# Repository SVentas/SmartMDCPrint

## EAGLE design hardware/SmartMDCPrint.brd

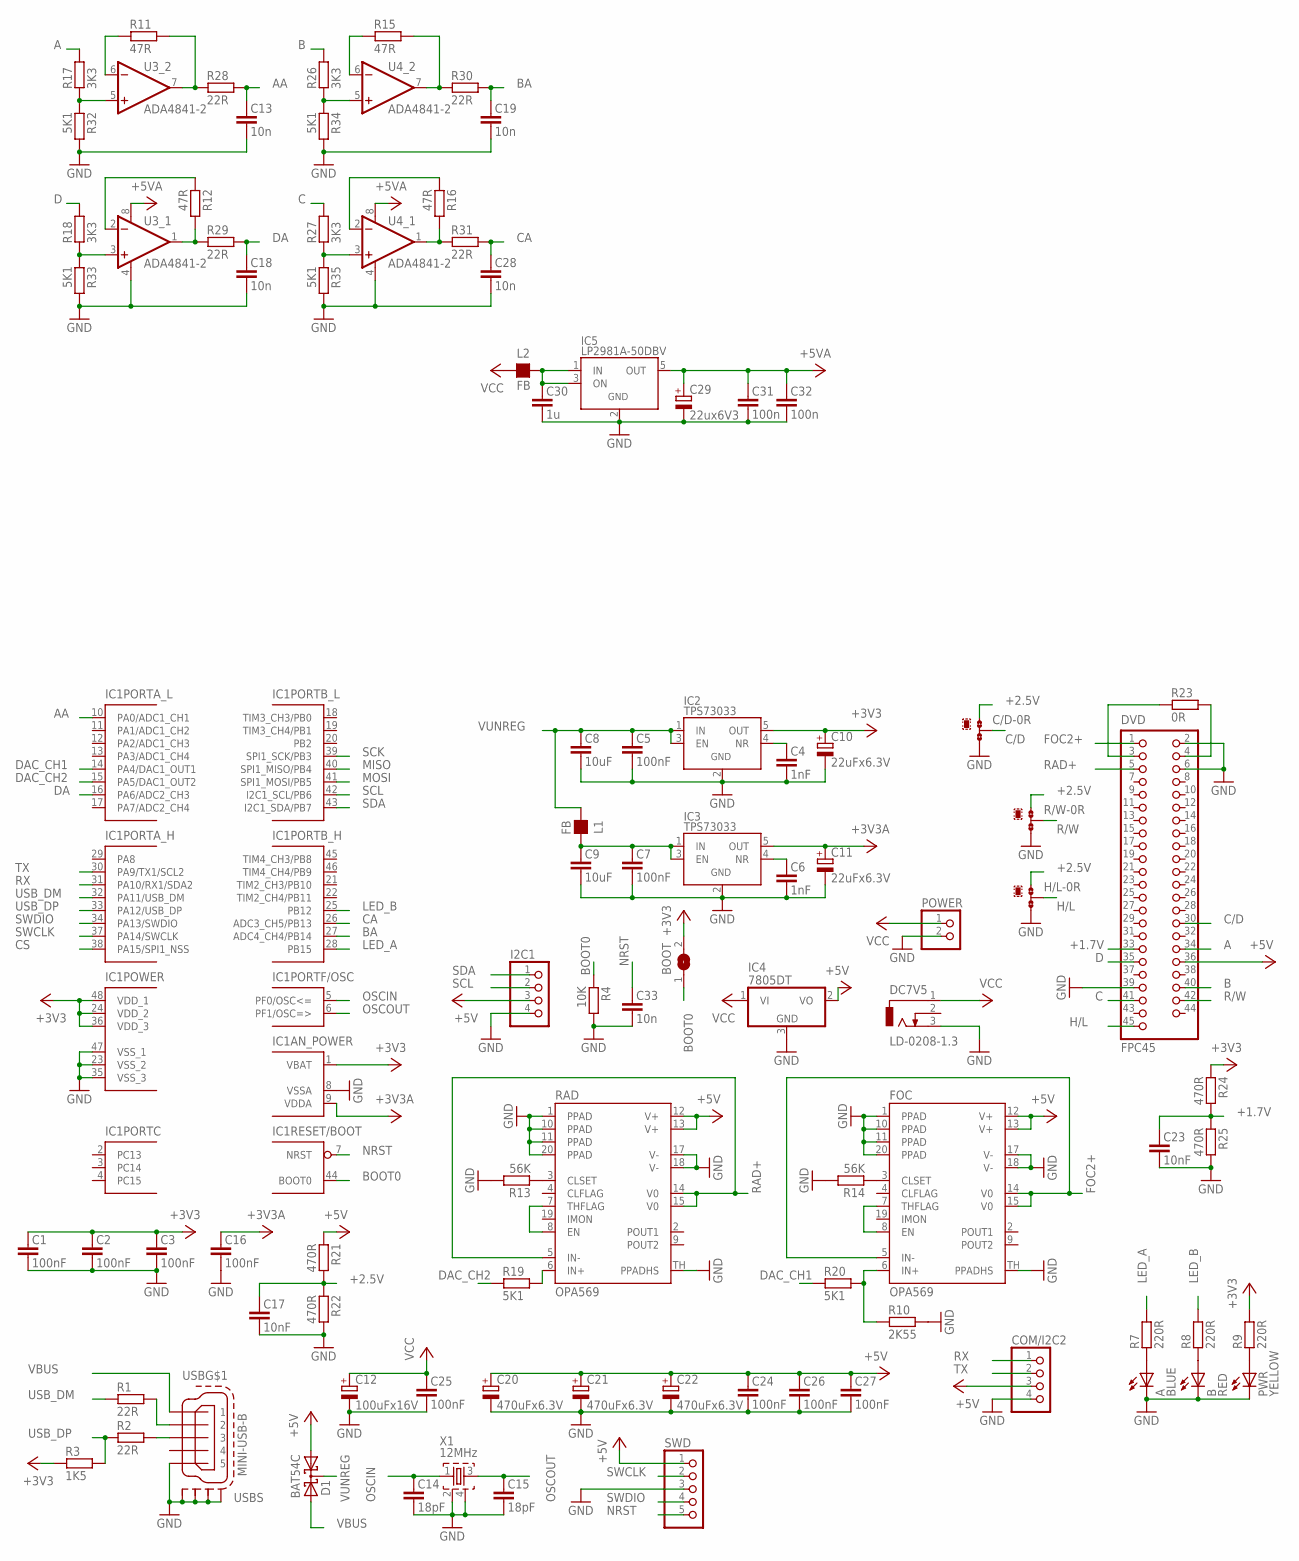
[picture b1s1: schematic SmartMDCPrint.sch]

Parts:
A: BLUE; CHIPLED_0805
B: RED; CHIPLED_0805
BOOT: SJ
C1, C2, C3, C5, C7, C16, C24, C25, C26, C27: 100nF; C0603G
C4, C6: 1nF; C0603G
C8, C9: 10uF; C0805
C10, C11: 22uFx6.3V; SMC_A
C12: 100uFx16V; E2,5-7
C13, C18, C19, C28, C33: 10n; C0603G
C14, C15: 18pF; C0603G
C17, C23: 10nF; C0603G
C20, C21, C22: 470uFx6.3V; SMC_D
C29: 22ux6V3; SMC_A
C30: 1u; C0603G
C31, C32: 100n; C0603G
C/D: 0R-JUMPA; A0R-JMP
COM/I2C2: PINHD-1X4; 1X04
D1: BAT54C; SOT23
DC7V5: LD-0208-1.3; LD-0208
DVD: FPC45
FOC: OPA569; SO-20
H/L: 0R-JUMPA; A0R-JMP
I2C1: PINHD-1X4; 1X04
IC1: STM32F303CCT6; LQFP48
IC2, IC3: TPS73033; SOT23-5
IC4: 7805DT; TO252
IC5: LP2981A-50DBV; SOT23-5
L1, L2: FB; L0603
POWER: PINHD-1X2; 1X02
PWR: YELLOW; CHIPLED_0805
R1, R2, R28, R29, R30, R31: 22R; R0603
R3: 1K5; R0603
R4: 10K; R0603G
R7, R8, R9: 220R; R0603
R10: 2K55; R0603G
R11, R12, R15, R16: 47R; R0603
R13, R14: 56K; R0603G
R17, R18, R26, R27: 3K3; R0603
R19, R20: 5K1; R0603
R21, R24: 470R; R0603
R22, R25: 470R; R0603G
R23: 0R; R0603
R32, R33, R34, R35: 5K1; R0603G
R/W: 0R-JUMPA; A0R-JMP
RAD: OPA569; SO-20
SWD: PINHD-1X5; 1X05
U3, U4: ADA4841-2; SOIC-8
USB: MINI-USB-B; 32005-201
X1: 12MHz; ABMM2

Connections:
+1.7V: C23.1, DVD.33, R24.2, R25.1
+2.5V: C17.1, C/D.1, H/L.1, R21.2, R22.1, R/W.1
+3V3: BOOT.2, C1.1, C2.1, C3.1, C10.+, IC1.1 (VBAT), IC1.24 (VDD_2), IC1.36 (VDD_3), IC1.48 (VDD_1), IC2.5 (OUT), R3.1, R9.2, R24.1
+3V3A: C11.+, C16.1, IC1.9 (VDDA), IC3.5 (OUT)
+5V: C20.+, C21.+, C22.+, C24.1, C26.1, C27.1, COM/I2C2.3, D1.1 (A1), DVD.36, FOC.12 (V+), FOC.13 (V+), I2C1.3, IC4.2 (VO), R21.1, RAD.12 (V+), RAD.13 (V+), SWD.1
+5VA: C29.+, C31.1, C32.1, IC5.5 (OUT), U3.8 (V+), U4.8 (V+)
A: DVD.34, R17.2
AA: C13.1, IC1.10 (PA0/ADC1_CH1), R28.2
B: DVD.40, R26.2
BA: C19.1, IC1.27 (ADC4_CH4/PB14), R30.2
BOOT0: BOOT.1, IC1.44 (BOOT0), R4.1
C: DVD.41, R27.2
C/D: C/D.2, DVD.30
CA: C28.1, IC1.26 (ADC3_CH5/PB13), R31.2
CS: IC1.38 (PA15/SPI1_NSS)
D: DVD.35, R18.2
DA: C18.1, IC1.16 (PA6/ADC2_CH3), R29.2
DAC_CH1: IC1.14 (PA4/DAC1_OUT1), R20.1
DAC_CH2: IC1.15 (PA5/DAC1_OUT2), R19.1
FOC2+: DVD.1, FOC.5 (IN-), FOC.14 (V0), FOC.15 (V0)
GND: A.C, B.C, C1.2, C2.2, C3.2, C4.2, C5.2, C6.2, C7.2, C8.2, C9.2, C10.-, C11.-, C12.-, C13.2, C14.2, C15.2, C16.2, C17.2, C18.2, C19.2, C20.-, C21.-, C22.-, C23.2, C24.2, C25.2, C26.2, C27.2, C28.2, C29.-, C30.2, C31.2, C32.2, C33.2, C/D.3, COM/I2C2.4, DC7V5.3, DVD.2, DVD.6, DVD.39, FOC.1 (PPAD), FOC.10 (PPAD), FOC.11 (PPAD), FOC.17 (V-), FOC.18 (V-), FOC.20 (PPAD), FOC.TH (PPADHS), H/L.3, I2C1.4, IC1.8 (VSSA), IC1.23 (VSS_2), IC1.35 (VSS_3), IC1.47 (VSS_1), IC2.2 (GND), IC3.2 (GND), IC4.3 (GND), IC5.2 (GND), POWER.2, PWR.C, R4.2, R10.2, R13.2, R14.2, R22.2, R25.2, R32.2, R33.2, R34.2, R35.2, R/W.3, RAD.1 (PPAD), RAD.10 (PPAD), RAD.11 (PPAD), RAD.17 (V-), RAD.18 (V-), RAD.20 (PPAD), RAD.TH (PPADHS), SWD.3, U3.4 (V-), U4.4 (V-), USB.5, USB.M1 (S1), USB.M2 (S2), USB.M3 (S3), USB.M4 (S4), X1.2, X1.4
H/L: DVD.45, H/L.2
LED_A: IC1.28 (PB15), R7.2
LED_B: IC1.25 (PB12), R8.2
MISO: IC1.40 (SPI1_MISO/PB4)
MOSI: IC1.41 (SPI1_MOSI/PB5)
unnamed: C7.1, C9.1, IC3.1 (IN), IC3.3 (EN), L1.2
unnamed: R1.2, USB.2
unnamed: R2.2, USB.3
unnamed: R11.2, R28.1, U3.7 (OUT)
unnamed: A.A, R7.1
unnamed: B.A, R8.1
unnamed: C4.1, IC2.4 (NR)
unnamed: C6.1, IC3.4 (NR)
unnamed: PWR.A, R9.1
unnamed: R12.2, R29.1, U3.1 (OUT)
unnamed: R13.1, RAD.3 (CLSET)
unnamed: R19.2, RAD.6 (IN+)
unnamed: FOC.6 (IN+), R10.1, R20.2
unnamed: R15.2, R30.1, U4.7 (OUT)
unnamed: DVD.3, R23.1
unnamed: R16.2, R31.1, U4.1 (OUT)
unnamed: FOC.7 (THFLAG), FOC.8 (EN)
unnamed: FOC.3 (CLSET), R14.1
unnamed: R11.1, U3.6 (-IN)
unnamed: R15.1, U4.6 (-IN)
unnamed: R16.1, U4.2 (-IN)
unnamed: R12.1, U3.2 (-IN)
unnamed: R17.1, R32.1, U3.5 (+IN)
unnamed: DVD.4, R23.2
unnamed: R18.1, R33.1, U3.3 (+IN)
unnamed: R26.1, R34.1, U4.5 (+IN)
unnamed: R27.1, R35.1, U4.3 (+IN)
unnamed: C30.1, IC5.1 (IN), IC5.3 (ON), L2.2
unnamed: RAD.7 (THFLAG), RAD.8 (EN)
NRST: C33.1, IC1.7 (NRST), SWD.5
OSCIN: C14.1, IC1.5 (PF0/OSC<=), X1.1
OSCOUT: C15.1, IC1.6 (PF1/OSC=>), X1.3
R/W: DVD.42, R/W.2
RAD+: DVD.5, RAD.5 (IN-), RAD.14 (V0), RAD.15 (V0)
RX: COM/I2C2.1, IC1.31 (PA10/RX1/SDA2)
SCK: IC1.39 (SPI1_SCK/PB3)
SCL: I2C1.2, IC1.42 (I2C1_SCL/PB6)
SDA: I2C1.1, IC1.43 (I2C1_SDA/PB7)
SWCLK: IC1.37 (PA14/SWCLK), SWD.2
SWDIO: IC1.34 (PA13/SWDIO), SWD.4
TX: COM/I2C2.2, IC1.30 (PA9/TX1/SCL2)
USB_DM: IC1.32 (PA11/USB_DM), R1.1
USB_DP: IC1.33 (PA12/USB_DP), R2.1, R3.2
VBUS: D1.2 (A2), USB.1
VCC: C12.+, C25.1, DC7V5.1, IC4.1 (VI), L2.1, POWER.1
VUNREG: C5.1, C8.1, D1.3 (CC), IC2.1 (IN), IC2.3 (EN), L1.1

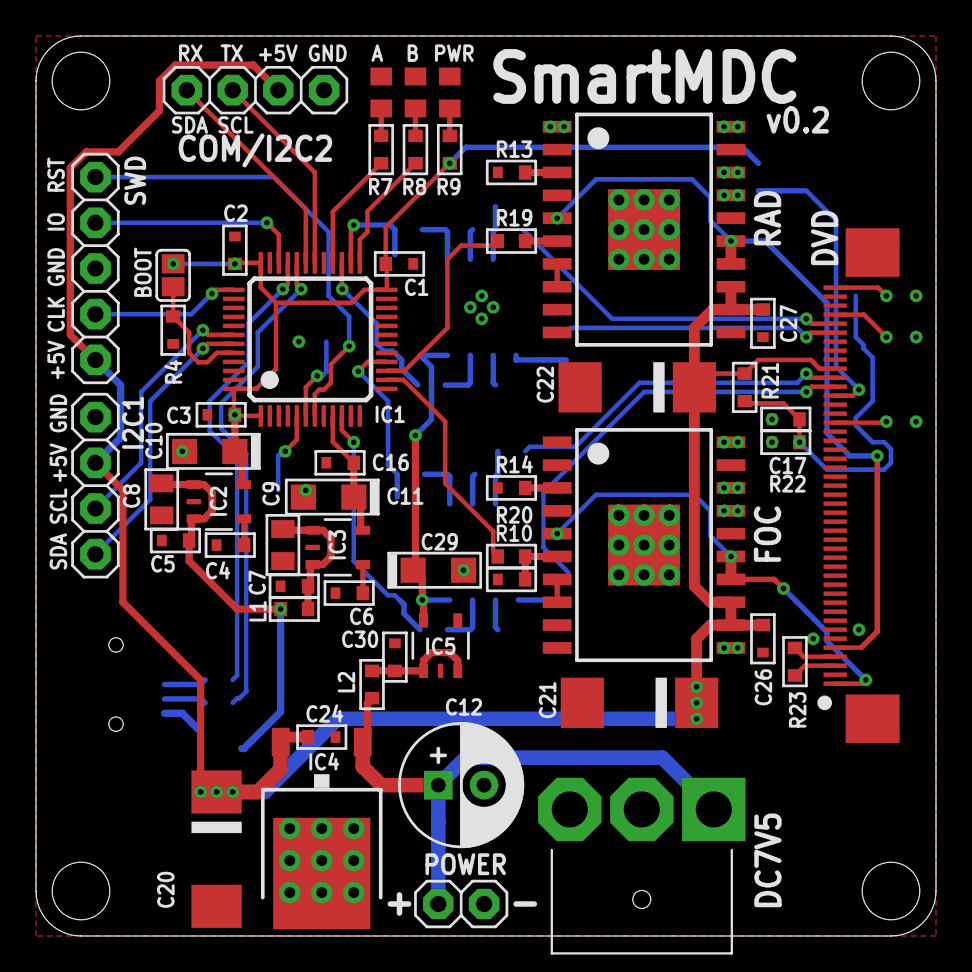
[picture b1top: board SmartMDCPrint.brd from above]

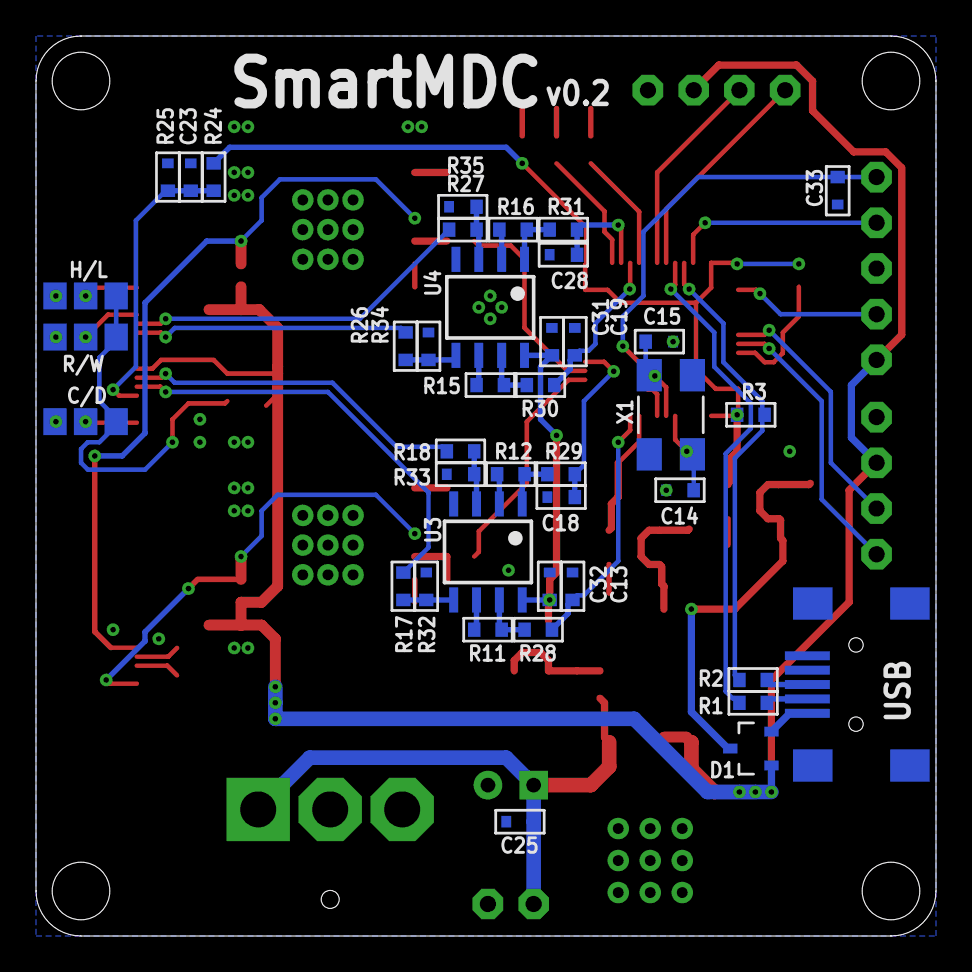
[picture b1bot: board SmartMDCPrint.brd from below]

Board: 2 copper layers, 50.0 x 50.0 mm, 93 parts (40 on the bottom side), 68 nets.

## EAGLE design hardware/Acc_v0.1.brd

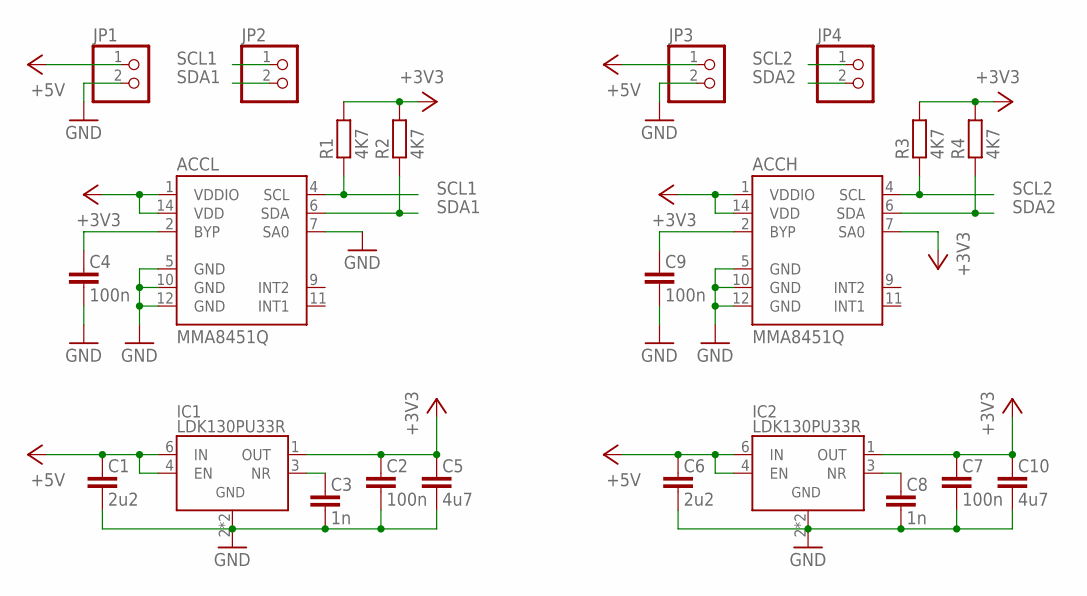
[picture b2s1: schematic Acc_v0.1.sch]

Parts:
ACCH: MMA8451Q; QFN-16
ACCL: MMA8451Q; QFN-16
C1, C6: 2u2; C0603G
C2, C4, C7, C9: 100n; C0603G
C3, C8: 1n; C0603G
C5, C10: 4u7; C0603G
IC1, IC2: LDK130PU33R; DFN6L
JP1, JP2, JP3, JP4: PINHD-1X2/SMD; 1X02S
R1, R2, R3, R4: 4K7; R0603

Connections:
+3V3: ACCH.1 (VDDIO), ACCH.7 (SA0), ACCH.14 (VDD), ACCL.1 (VDDIO), ACCL.14 (VDD), C2.1, C5.1, C7.1, C10.1, IC1.1 (OUT), IC2.1 (OUT), R1.2, R2.2, R3.2, R4.2
+5V: C1.1, C6.1, IC1.4 (EN), IC1.6 (IN), IC2.4 (EN), IC2.6 (IN), JP1.1, JP3.1
GND: ACCH.5 (GND), ACCH.10 (GND), ACCH.12 (GND), ACCL.5 (GND), ACCL.7 (SA0), ACCL.10 (GND), ACCL.12 (GND), C1.2, C2.2, C3.2, C4.2, C5.2, C6.2, C7.2, C8.2, C9.2, C10.2, IC1.2 (GND), IC1.5 (GND), IC2.2 (GND), IC2.5 (GND), JP1.2, JP3.2
unnamed: C8.1, IC2.3 (NR)
unnamed: ACCH.2 (BYP), C9.1
unnamed: C3.1, IC1.3 (NR)
unnamed: ACCL.2 (BYP), C4.1
SCL1: ACCL.4 (SCL), JP2.1, R1.1
SCL2: ACCH.4 (SCL), JP4.1, R3.1
SDA1: ACCL.6 (SDA), JP2.2, R2.1
SDA2: ACCH.6 (SDA), JP4.2, R4.1

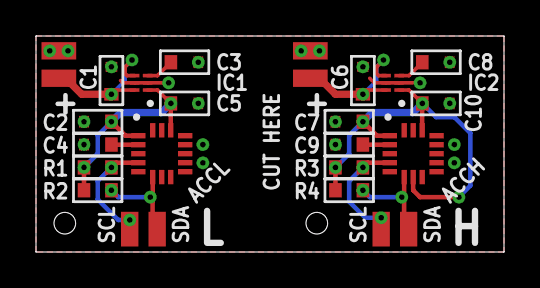
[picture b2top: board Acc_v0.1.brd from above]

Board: 2 copper layers, 26.0 x 12.0 mm, 22 parts (0 on the bottom side), 11 nets.

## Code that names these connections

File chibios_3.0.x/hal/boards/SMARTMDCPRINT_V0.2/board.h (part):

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/*
 * GPIOA setup:
 *
 * PA0  - ADC1_CH1                  (analog floating).
 * PA1  - PIN1                      (input floating).
 * PA2  - PIN2                      (input floating).
 * PA3  - PIN3                      (input floating).
 * PA4  - DAC_CH1                   (analog floating).
 * PA5  - DAC_CH2                   (analog floating).
 * PA6  - ADC2_CH3                  (analog floating).
 * PA7  - PIN7                      (input floating).
 * PA8  - PIN8                      (input floating).
 * PA9  - PIN9                      (alternate 4).
 * PA10 - PIN10                     (alternate 4).
 * PA11 - USB_DM                    (alternate 14).
 * PA12 - USB_DP                    (alternate 14).
 * PA13 - SWDIO                     (alternate 0).
 * PA14 - SWCLK                     (alternate 0).
 * PA15 - PIN15                     (input floating).
 */
#define VAL_GPIOA_MODER             (PIN_MODE_ANALOG(GPIOA_ADC1_CH1) |      \
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 * PB3  - PIN3                      (input floating).
 * PB4  - PIN4                      (input floating).
 * PB5  - PIN5                      (input floating).
 * PB6  - I2C1_SCL                  (alternate 4).
 * PB7  - I2C1_SDA                  (alternate 4).
 * PB8  - PIN8                      (input floating).
 * PB9  - PIN9                      (input floating).
 * PB10 - PIN10                     (input floating).
 * PB11 - PIN11                     (input floating).
 * PB12 - LED_B                     (output pushpull).
 * PB13 - ADC3_CH5                  (analog floating).
 * PB14 - ADC4_CH4                  (analog floating).
 * PB15 - LED_A                     (output pushpull).
 */
#define VAL_GPIOB_MODER             (PIN_MODE_INPUT(GPIOB_PIN0) |           \
                                     PIN_MODE_INPUT(GPIOB_PIN1) |           \
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/*
 * GPIOF setup:
 *
 * PF0  - OSC_IN                    (input floating).
 * PF1  - OSC_OUT                   (input floating).
 * PF2  - PIN2                      (input floating).
 * PF3  - PIN3                      (input floating).
 * PF4  - PIN4                      (input floating).
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
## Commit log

2015-10-13 :boom::camel: Added .gitattributes & .gitignore files
2015-10-13 Content added.
2015-10-13 Bug in ADC cb code removed.
2015-10-16 Telemetry added.
2015-10-19 Telemetry improved.
2015-10-21 ADC synchronization added.
2015-10-31 Code optimization. Default configuration changed.
2015-11-04 Some cleaning.
2015-11-04 ADC speed changed.
2015-11-05 Sampling speed adjusted.
2015-11-13 ChibiOS update.
2015-11-13 Synchronization model changed.
2015-11-13 Reboot to bootloader command added.
2015-11-13 Accel data handling changed.

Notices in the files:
chibios_3.0.x/hal/boards/SMARTMDCPRINT_V0.2/board.h:
VauProject - Copyright (C) 2013-2015 Sarunas Vaitekonis
Licensed under the Apache License, Version 2.0 (the "License");
